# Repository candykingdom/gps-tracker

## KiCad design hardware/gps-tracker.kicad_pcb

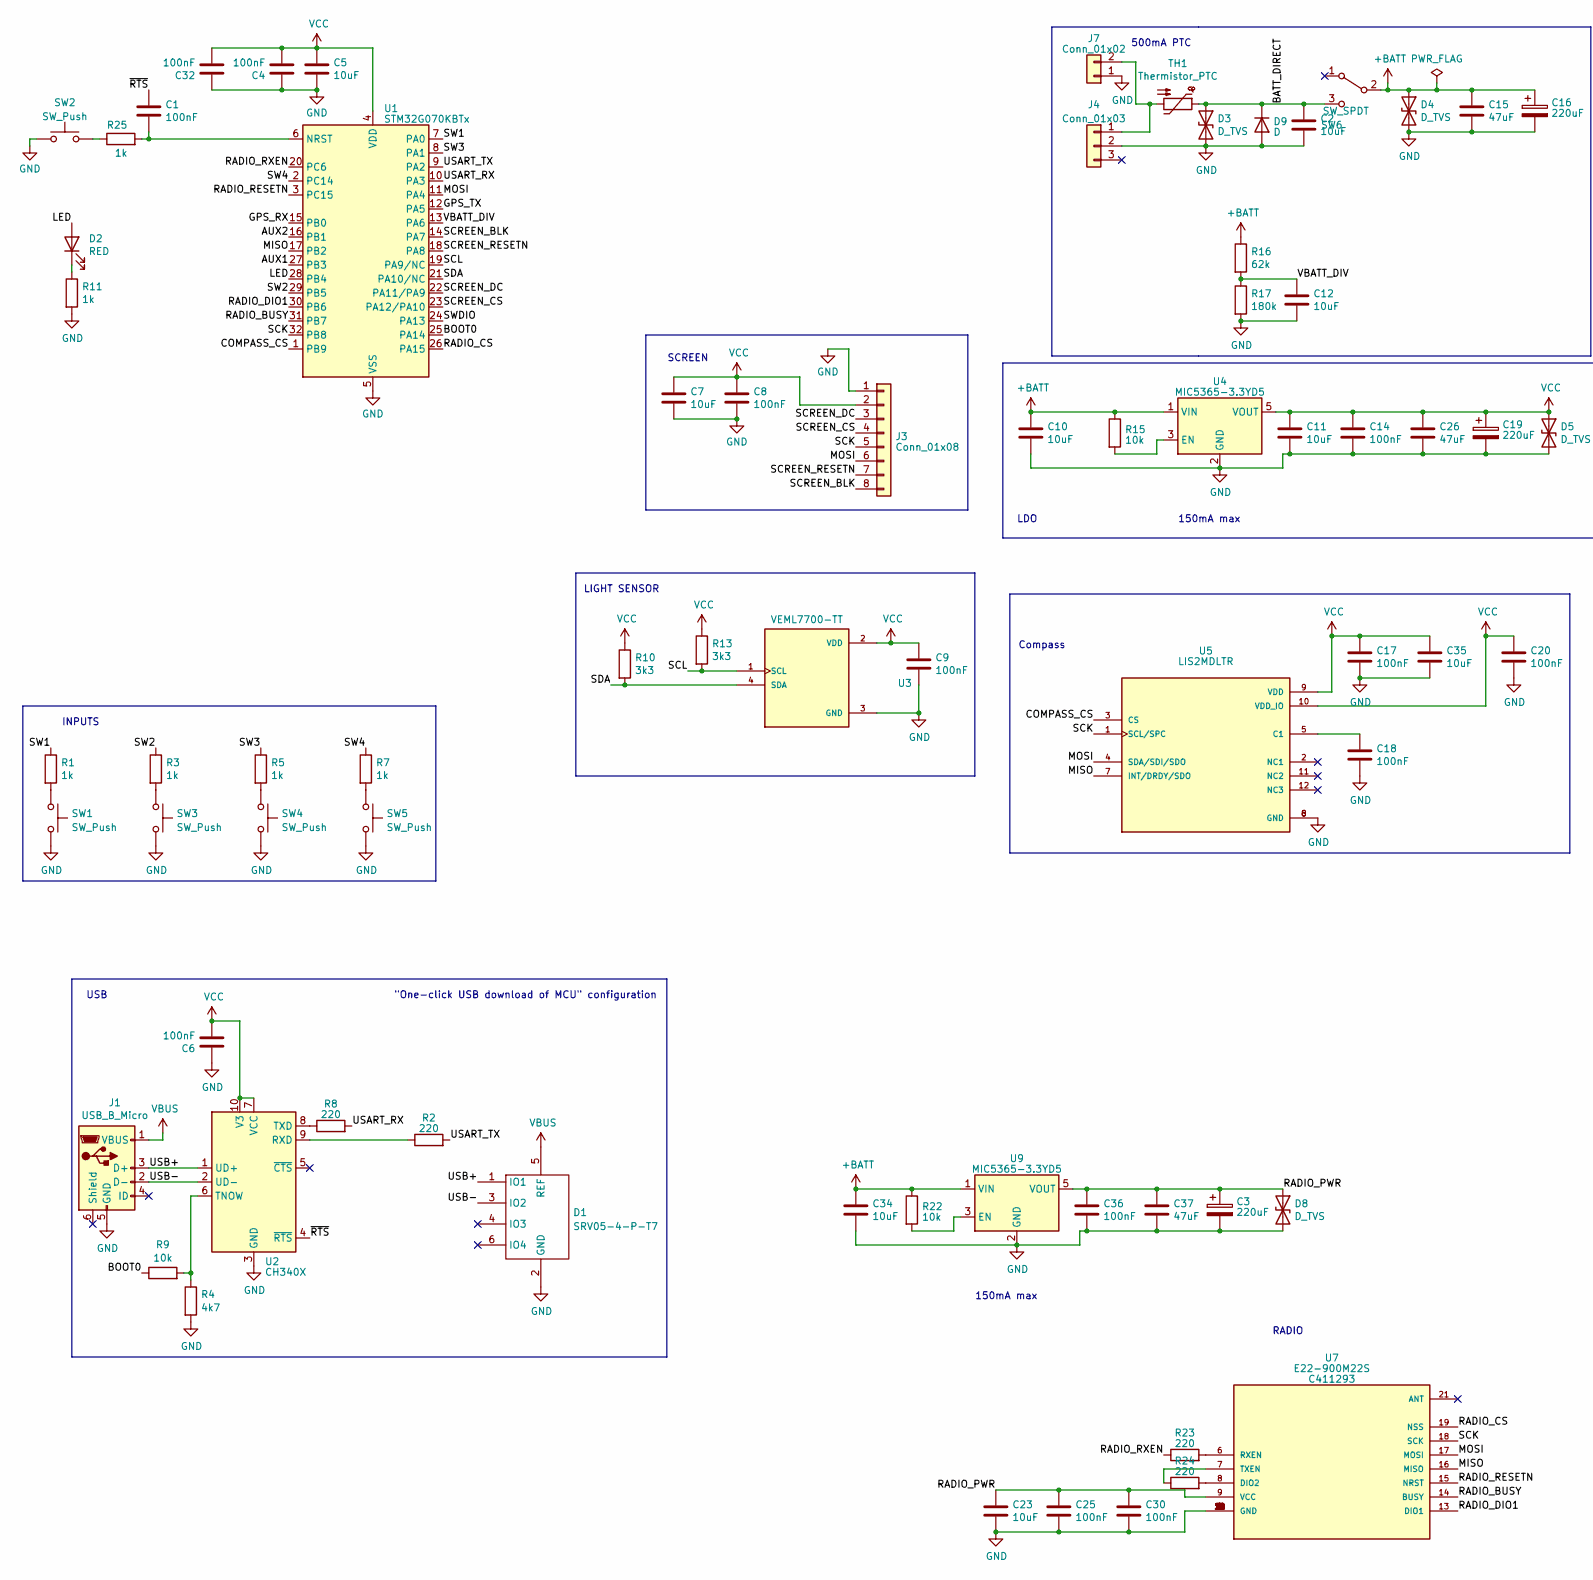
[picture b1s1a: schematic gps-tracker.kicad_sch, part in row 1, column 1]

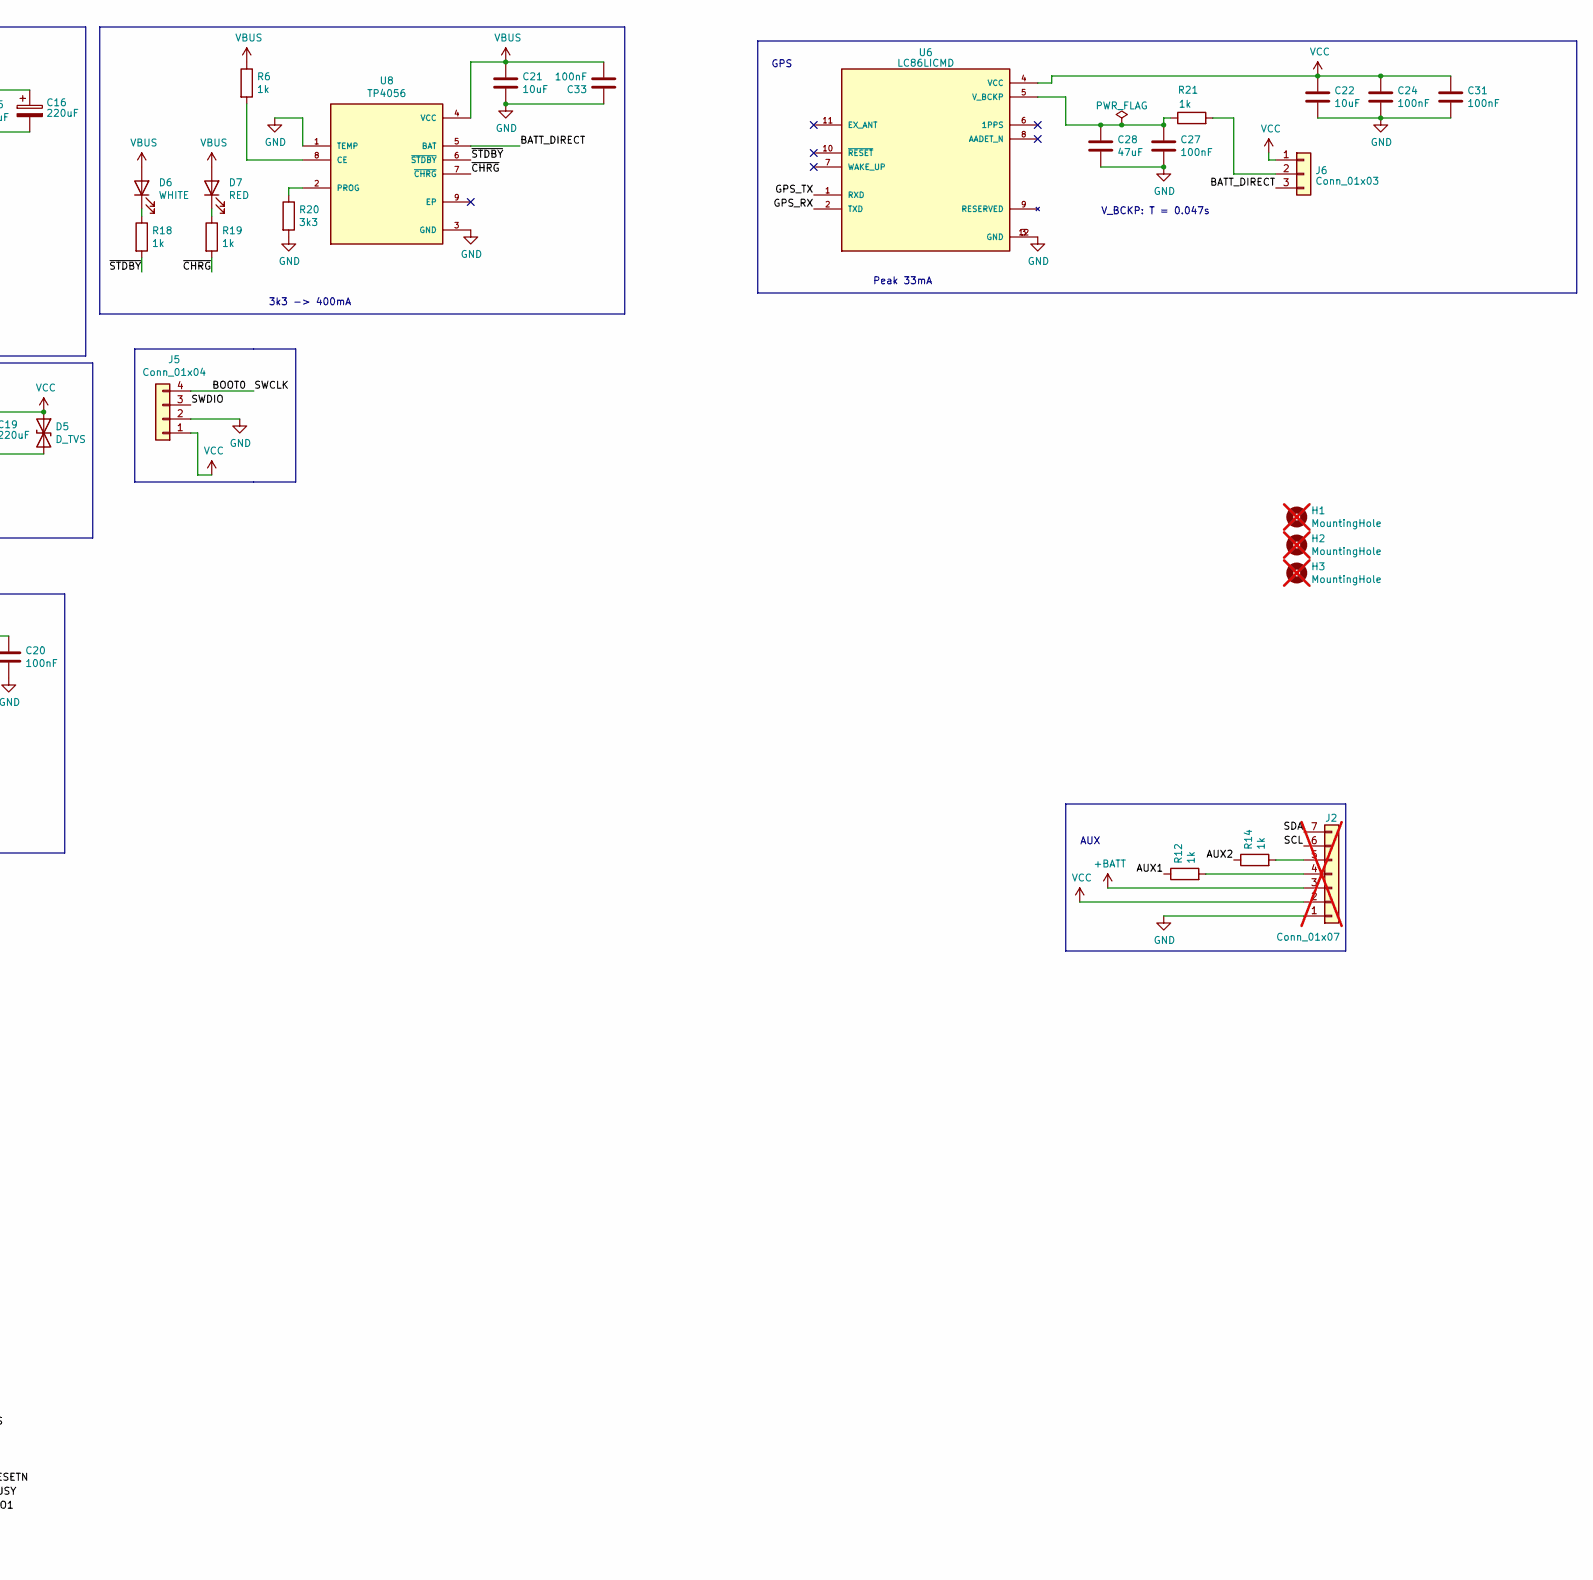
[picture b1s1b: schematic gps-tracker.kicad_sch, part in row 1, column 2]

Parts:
C1, C4, C6, C8, C9, C14, C17, C18, C20, C24, C25, C27, C30, C31, C32, C33, C36: 100nF; C_0402_1005Metric; LCSC C307331
C2, C5, C7, C10, C11, C12, C21, C22, C23, C34, C35: 10uF; C_0603_1608Metric; LCSC C96446
C3, C16, C19: 220uF; CP_Radial_D10.0mm_P5.00mm; MPN ER1E221MP51007RU
C15, C26, C28, C37: 47uF; C_1206_3216Metric; LCSC C96123
D1: SRV05-4-P-T7; SOT-23-6; LCSC C85364
D2, D7: RED; LED_0603_1608Metric; LCSC C2286
D3, D4, D5, D8: D_TVS; D_SOD-123F; LCSC C2990473
D6: WHITE; LED_0603_1608Metric; LCSC C2290
D9: D; D_SMA; LCSC C8678
H1, H2, H3: MountingHole; MountingHole_3.2mm_M3; not fitted
J1: USB_B_Micro; FRAMATOME_10118194-0001LF_fixed_bridges; LCSC C132563
J2: Conn_01x07; PinHeader_1x07_P2.54mm_Vertical; not fitted
J3: Conn_01x08; PinHeader_1x08_P2.54mm_Vertical
J4: Conn_01x03; MiniPV_78208-X03XXX_1x03_P2.54mm_Polarized_Horizontal
J5: Conn_01x04; PinHeader_1x04_P2.54mm_Vertical
J6: Conn_01x03; PinHeader_1x03_P2.54mm_Vertical
J7: Conn_01x02; JST_Micro_1x02_P1.25mm_Horizontal
R1, R3, R5, R6, R7, R11, R18, R19, R25: 1k; R_0402_1005Metric; LCSC C11702
R2, R8, R23, R24: 220; R_0402_1005Metric; LCSC C25091
R4: 4k7; R_0402_1005Metric; LCSC C25900
R9, R15, R22: 10k; R_0402_1005Metric; LCSC C25744
R10, R13, R20: 3k3; R_0603_1608Metric; LCSC C22978
R12, R14, R21: 1k; R_0603_1608Metric; LCSC C21190
R16: 62k; R_0603_1608Metric; LCSC C23221
R17: 180k; R_0603_1608Metric; LCSC C22827
SW1, SW2, SW3, SW4, SW5: SW_Push; SW_TACTILE_5.1MM_TS-1187A-C-D-B; LCSC C318884
SW6: SW_SPDT; SS-12D03-G5; LCSC C698226
TH1: Thermistor_PTC; Fuse_0805_2012Metric; LCSC C269104
U1: STM32G070KBTx; LQFP-32_7x7mm_P0.8mm; LCSC C529339
U2: CH340X; MSOP-10_3x3mm_P0.5mm; LCSC C3035748
U3: VEML7700-TT; VISHAY_VEML7700-TT; PARTREV 1.6
U4, U9: MIC5365-3.3YD5; SOT-23-5; MPN MIC5365-3.3YD5
U5: LIS2MDLTR; PQFN50P200X200X70-12N; PARTREV Rev 5; LCSC C919695
U6: LC86LICMD; MODULE_LC86LICMD; MPN LC86LICMD
U7: E22-900M22S; LCSC C411293
U8: TP4056; SOP-8_3.9x4.9mm_P1.27mm_Thermal; LCSC C382139

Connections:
+BATT: C10.2, C15.2, C16.1, C34.2, D4.1 (A1), J2.3, R15.1, R16.1, R22.1, SW6.2 (B), U4.1 (VIN), U9.1 (VIN)
/AUX1: R12.1, U1.27 (PB3)
/AUX2: R14.1, U1.16 (PB1)
/BATT_DIRECT: C2.2, D3.1 (A1), D9.1 (K), J6.3, SW6.3 (C), TH1.1, U8.5 (BAT)
/BOOT0: J5.4, R9.1, U1.25 (PA14)
/COMPASS_CS: U1.1 (PB9), U5.3 (CS)
/GPS_RX: U1.15 (PB0), U6.2 (TXD)
/GPS_TX: U1.12 (PA5), U6.1 (RXD)
/LED: D2.2 (A), U1.28 (PB4)
/MISO: U1.17 (PB2), U5.7 (INT/DRDY/SDO), U7.16 (MISO)
/MOSI: J3.6, U1.11 (PA4), U5.4 (SDA/SDI/SDO), U7.17 (MOSI)
/RADIO_BUSY: U1.31 (PB7), U7.14 (BUSY)
/RADIO_CS: U1.26 (PA15), U7.19 (NSS)
/RADIO_DIO1: U1.30 (PB6), U7.13 (DIO1)
/RADIO_PWR: C3.1, C23.2, C25.1, C30.1, C36.1, C37.2, D8.1 (A1), U7.9 (VCC), U9.5 (VOUT)
/RADIO_RESETN: U1.3 (PC15), U7.15 (NRST)
/RADIO_RXEN: R23.1, U1.20 (PC6)
/SCK: J3.5, U1.32 (PB8), U5.1 (SCL/SPC), U7.18 (SCK)
/SCL: J2.6, R13.2, U1.19 (PA9/NC), U3.1 (SCL)
/SCREEN_BLK: J3.8, U1.14 (PA7)
/SCREEN_CS: J3.4, U1.23 (PA12/PA10)
/SCREEN_DC: J3.3, U1.22 (PA11/PA9)
/SCREEN_RESETN: J3.7, U1.18 (PA8)
/SDA: J2.7, R10.2, U1.21 (PA10/NC), U3.4 (SDA)
/SW1: R1.1, U1.7 (PA0)
/SW2: R3.1, U1.29 (PB5)
/SW3: R5.1, U1.8 (PA1)
/SW4: R7.1, U1.2 (PC14)
/SWDIO: J5.3, U1.24 (PA13)
/USART_RX: R8.2, U1.10 (PA3)
/USART_TX: R2.2, U1.9 (PA2)
/USB+: D1.1 (IO1), J1.3 (D+), U2.1 (UD+)
/USB-: D1.3 (IO2), J1.2 (D-), U2.2 (UD-)
/VBATT_DIV: C12.2, R16.2, R17.1, U1.13 (PA6)
/~CHRG: R19.2, U8.7 (~CHRG)
/~RTS: C1.1, U2.4 (~RTS)
/~STDBY: R18.2, U8.6 (~STDBY)
GND: C2.1, C3.2, C4.1, C5.2, C6.1, C7.1, C8.2, C9.2, C10.1, C11.1, C12.1, C14.2, C15.1, C16.2, C17.2, C18.2, C19.2, C20.2, C21.1, C22.1, C23.1, C24.2, C25.2, C26.1, C27.2, C28.1, C30.2, C31.2, C32.1, C33.1, C34.1, C35.1, C36.2, C37.1, D1.2 (GND), D3.2 (A2), D4.2 (A2), D5.2 (A2), D8.2 (A2), D9.2 (A), J1.5 (GND), J2.1, J3.1, J4.2, J5.2, J7.1, R4.2, R11.2, R17.2, R20.2, SW1.2, SW2.1, SW3.2, SW4.2, SW5.2, U1.5 (VSS), U2.3 (GND), U3.3 (GND), U4.2 (GND), U5.6 (GND), U5.8 (GND), U6.3 (GND), U6.12 (GND), U7.1 (GND), U7.2 (GND), U7.3 (GND), U7.4 (GND), U7.5 (GND), U7.10 (GND), U7.11 (GND), U7.12 (GND), U7.20 (GND), U7.22 (GND), U8.1 (TEMP), U8.3 (GND), U9.2 (GND)
unnamed: D2.1 (K), R11.1
unnamed: D6.1 (K), R18.1
unnamed: D7.1 (K), R19.1
unnamed: J2.4, R12.2
unnamed: J2.5, R14.2
unnamed: J4.1, J7.2, TH1.2
unnamed: J6.2, R21.2
unnamed: R1.2, SW1.1
unnamed: R3.2, SW3.1
unnamed: R5.2, SW4.1
unnamed: R7.2, SW5.1
unnamed: R25.1, SW2.2
unnamed: C1.2, R25.2, U1.6 (NRST)
unnamed: R2.1, U2.9 (RXD)
unnamed: R4.1, R9.2, U2.6 (TNOW)
unnamed: R8.1, U2.8 (TXD)
unnamed: R15.2, U4.3 (EN)
unnamed: C18.1, U5.5 (C1)
unnamed: C27.1, C28.2, R21.1, U6.5 (V_BCKP)
unnamed: R24.2, U7.8 (DIO2)
unnamed: R23.2, U7.6 (RXEN)
unnamed: R24.1, U7.7 (TXEN)
unnamed: R6.2, U8.8 (CE)
unnamed: R20.1, U8.2 (PROG)
unnamed: R22.2, U9.3 (EN)
VBUS: C21.2, C33.2, D1.5 (REF), D6.2 (A), D7.2 (A), J1.1 (VBUS), R6.1, U8.4 (VCC)
VCC: C4.2, C5.1, C6.2, C7.2, C8.1, C9.1, C11.2, C14.1, C17.1, C19.1, C20.1, C22.2, C24.1, C26.2, C31.1, C32.2, C35.2, D5.1 (A1), J2.2, J3.2, J5.1, J6.1, R10.1, R13.1, U1.4 (VDD), U2.7 (VCC), U2.10 (V3), U3.2 (VDD), U4.5 (VOUT), U5.9 (VDD), U5.10 (VDD_IO), U6.4 (VCC)

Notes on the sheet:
Peak 33mA
RADIO
INPUTS
AUX
3k3 -> 400mA
USB
500mA PTC
LIGHT SENSOR
"One-click USB download of MCU" configuration
150mA max
GPS
Compass
V_BCKP: T = 0.047s
SCREEN
LDO

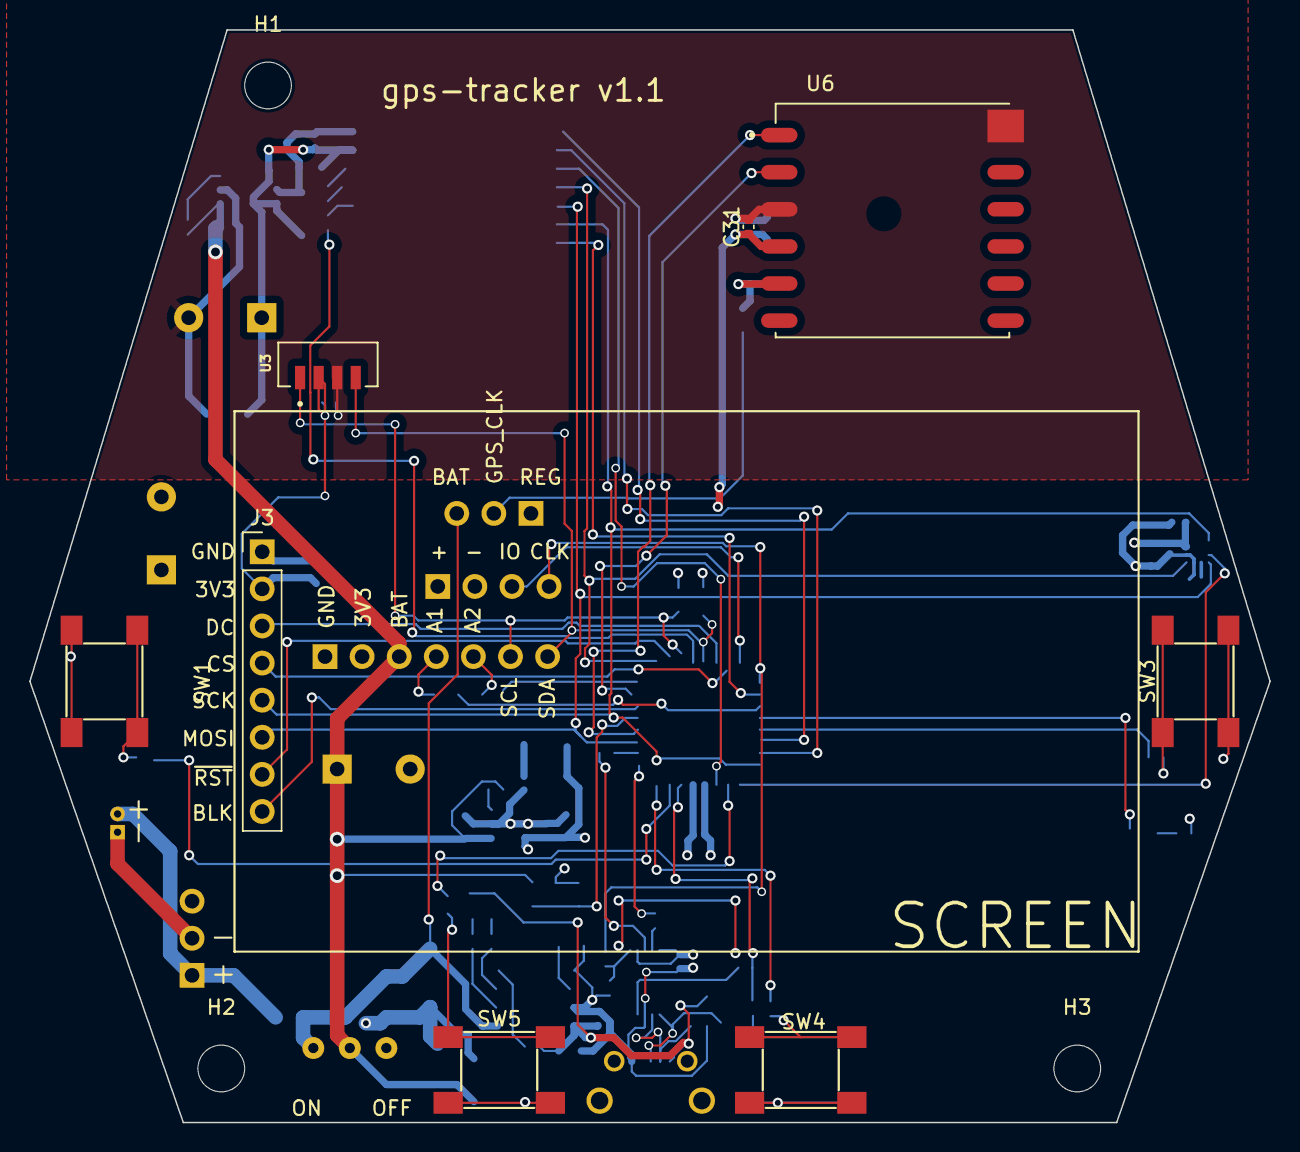
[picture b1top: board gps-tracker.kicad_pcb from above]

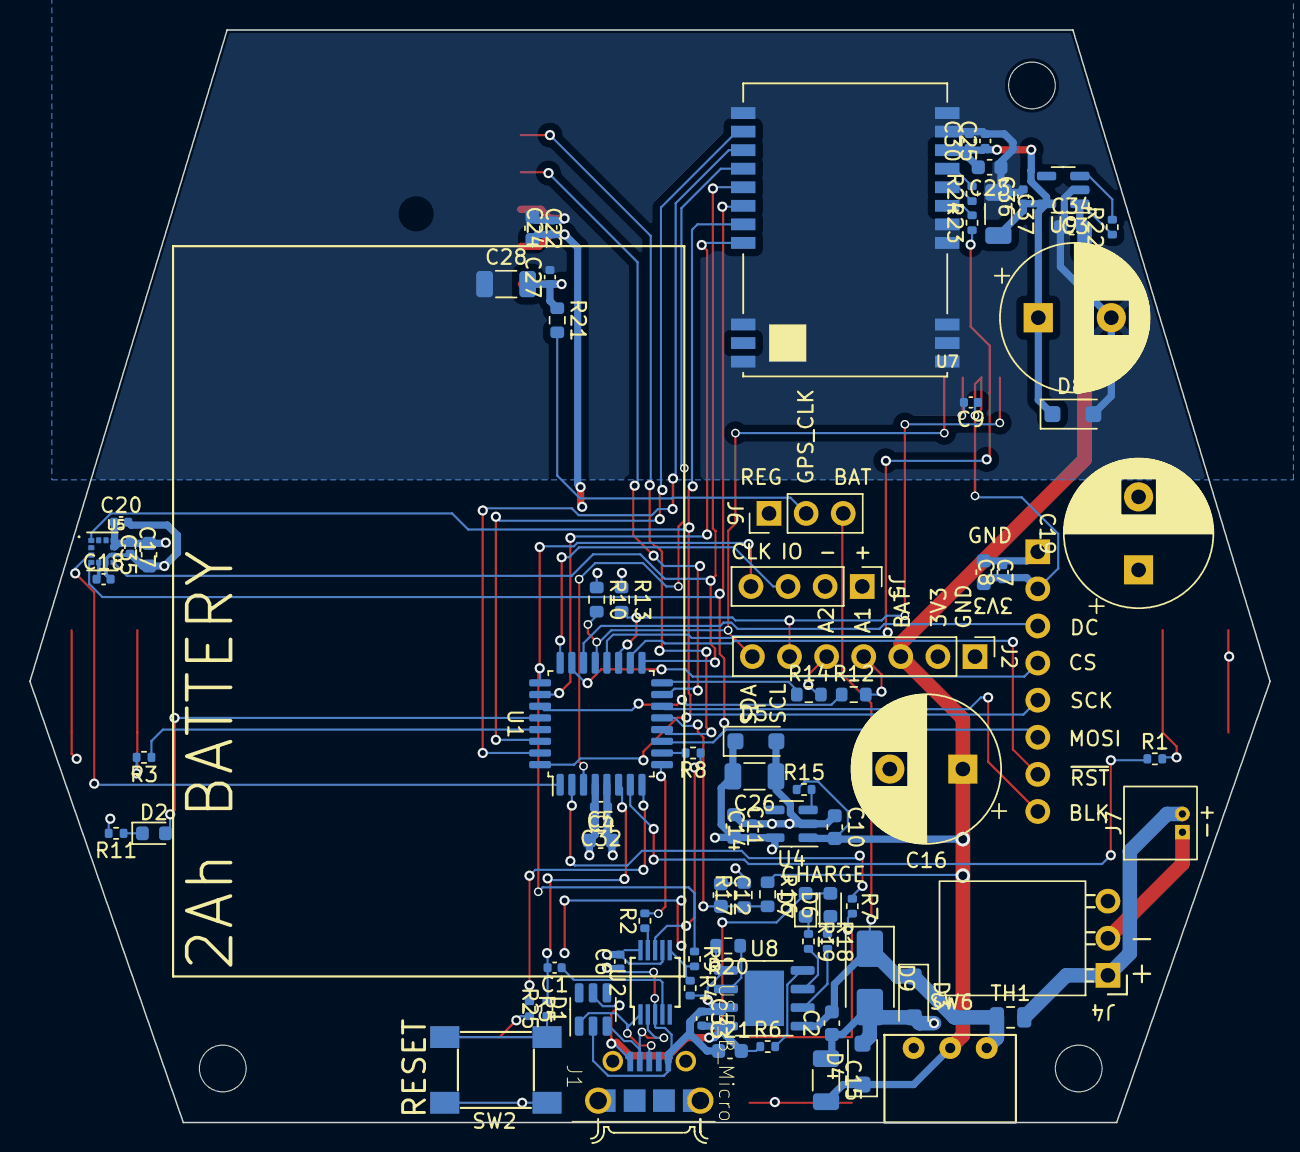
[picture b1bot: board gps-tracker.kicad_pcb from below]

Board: 4 copper layers, 84.9 x 74.8 mm, 95 parts (84 on the bottom side), 65 nets.

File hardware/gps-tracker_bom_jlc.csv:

"Comment","Designator","Footprint","LCSC Part #"
"100nF","C1,C4,C6,C8,C9,C14,C17,C18,C20,C24,C25,C27,C30,C31,C32,C33,C36","C_0402_1005Metric","C307331"
"10uF","C2,C5,C7,C10,C11,C12,C21,C22,C23,C34,C35","C_0603_1608Metric","C96446"
"47uF","C15,C26,C28,C37","C_1206_3216Metric","C96123"
"SRV05-4-P-T7","D1","SOT-23-6","C85364"
"RED","D2,D7","LED_0603_1608Metric","C2286"
"D_TVS","D3,D4,D5,D8","D_SOD-123F","C2990473"
"WHITE","D6","LED_0603_1608Metric","C2290"
"D","D9","D_SMA","C8678"
"USB_B_Micro","J1","FRAMATOME_10118194-0001LF_fixed_bridges","C132563"
"1k","R1,R3,R5,R6,R7,R11,R18,R19,R25","R_0402_1005Metric","C11702"
"220","R2,R8,R23,R24","R_0402_1005Metric","C25091"
"4k7","R4","R_0402_1005Metric","C25900"
"10k","R9,R15,R22","R_0402_1005Metric","C25744"
"3k3","R10,R13,R20","R_0603_1608Metric","C22978"
"1k","R12,R14,R21","R_0603_1608Metric","C21190"
"62k","R16","R_0603_1608Metric","C23221"
"180k","R17","R_0603_1608Metric","C22827"
"SW_Push","SW1,SW2,SW3,SW4,SW5","SW_TACTILE_5.1MM_TS-1187A-C-D-B","C318884"
"SW_SPDT","SW6","SS-12D03-G5","C698226"
"Thermistor_PTC","TH1","Fuse_0805_2012Metric","C269104"
"STM32G070KBTx","U1","LQFP-32_7x7mm_P0.8mm","C529339"
"CH340X","U2","MSOP-10_3x3mm_P0.5mm","C3035748"
"LIS2MDLTR","U5","PQFN50P200X200X70-12N","C919695"
"E22-900M22S","U7","E22-900M22S","C411293"
"TP4056","U8","SOP-8_3.9x4.9mm_P1.27mm_Thermal","C382139"

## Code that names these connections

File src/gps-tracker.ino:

#include <Adafruit_GFX.h>  // Core graphics library
#include <Adafruit_LTR329_LTR303.h>
#include <Adafruit_ST7789.h>  // Hardware-specific library for ST7789
#include <Arduino.h>
#include <RadioLib.h>
#include <TinyGPSPlus.h>

#include <algorithm>

#include "arduino-compass.h"
#include "arduino-gps.h"
#include "radio.h"

constexpr bool kUseScreen = false;

constexpr int kLed = PB4;

// SPI
constexpr int kMiso = PB2;
constexpr int kMosi = PA4;
constexpr int kSck = PB8;

// Radio
constexpr int kRadioCs = PA15;
constexpr int kRadioDio1 = PB6;
constexpr int kRadioBusy = PB7;
constexpr int kRadioRxen = PC6;

// Screen
constexpr int kScreenDc = PA11;
constexpr int kScreenCs = PA12;
constexpr int kScreenBlk = PA7;
constexpr int kScreenReset = PA8;
Adafruit_ST7789 screen = Adafruit_ST7789(kScreenCs, kScreenDc, kScreenReset);

// I2C
constexpr int kScl = PA9;
constexpr int kSda = PA10;

Adafruit_LTR303 light_sensor;
ArduinoCompass compass;
ArduinoGps gps;

SPISettings radio_spi_settings(10 * 1000 * 1000, MSBFIRST, SPI_MODE0);
SX1262 radio = new Module(kRadioCs, kRadioDio1, /*rst=*/RADIOLIB_NC,
                          /*gpio=*/kRadioBusy, SPI, radio_spi_settings);
volatile bool radio_idle = true;

void SetRadioIdle(void) {
  radio_idle = true;
  // digitalWrite(kLed, LOW);
}

void FatalError() {
  bool on = false;
  while (true) {
    digitalWrite(kLed, on);
    delay(100);
    on = !on;
  }
}

// http://www.hhhh.org/wiml/proj/nmeaxor.html
String withChecksum(String sentence) {
  bool started = false;
  char checksum = 0;
  for (uint32_t index = 0; index < sentence.length(); index++) {
    if (index > 0 && sentence[index - 1] == '$') {
      checksum = sentence[index];
      started = true;
      continue;  // Skip the rest of this loop iteration.
    }

    if (sentence[index] == '*') {
      break;  // Exit the loop.
    }

    // Ignore everything preceeding '$'.
    if (!started) {
      continue;  // Skip the rest of this loop iteration.
    }

    checksum = checksum xor sentence[index];
  }

  String sentenceWithChecksum =
      sentence + (checksum < 10 ? "0" : "") + String(checksum, HEX);
  return sentenceWithChecksum;
}

void ConfigureScreen() {
  screen.init(/*width=*/240, /*height=*/320);
  screen.setSPISpeed(20 * 1000 * 1000);
  screen.fillScreen(ST77XX_BLACK);
  screen.setTextSize(2);
  screen.setTextWrap(false);
}

void setup() {
  // check if nBOOT_SEL bit is set
  if (FLASH->OPTR & FLASH_OPTR_nBOOT_SEL) {
    // unlock flash/option
    FLASH->KEYR = 0x45670123;
    FLASH->KEYR = 0xCDEF89AB;
    FLASH->OPTKEYR = 0x08192A3B;
    FLASH->OPTKEYR = 0x4C5D6E7F;

    while (FLASH->SR & FLASH_SR_BSY1)
      ;

    // clear nBOOT_SEL bit
    FLASH->OPTR &= ~FLASH_OPTR_nBOOT_SEL;

    // write
    FLASH->CR |= FLASH_CR_OPTSTRT;
    while (FLASH->SR & FLASH_SR_BSY1)
      ;
  }

  pinMode(kLed, OUTPUT);
  // digitalWrite(kLed, HIGH);
  pinMode(kScreenBlk, OUTPUT);
  digitalWrite(kScreenBlk, HIGH);

  pinMode(kRadioRxen, OUTPUT);
  digitalWrite(kRadioRxen, HIGH);

  Serial2.begin(115200);
  Serial2.printf("Booting...\n");

  SPI.setMISO(kMiso);
  SPI.setMOSI(kMosi);
  SPI.setSCLK(kSck);

  delay(100);
  // TODO: re-enable when light sensor can be soldered reliably
  // Wire.setSCL(kScl);
  // Wire.setSDA(kSda);
  // Wire.begin();
  // Wire.setClock(100000);
  // if (!light_sensor.begin()) {
  //   Serial2.println("Light sensor init failed");
  //   FatalError();
  // }
  // light_sensor.setGain(LTR3XX_GAIN_1);
  // light_sensor.setIntegrationTime(LTR3XX_INTEGTIME_400);
  // light_sensor.setMeasurementRate(LTR3XX_MEASRATE_500);

  if (!compass.Begin()) {
    Serial2.println("Failed to initialize compass");
    FatalError();
  }

  if (!gps.Begin()) {
    Serial2.println("Failed to initialize GPS");
    FatalError();
  }

  // Configure radio
  Serial2.print("Initializing radio... ");
  int state = radio.begin(/*freq=*/915.0, /*bw*/ 125, /*sf=*/9, /*cr=*/7,
                          /*syncWord=*/18, /*power=*/22, /*preambleLength=*/8,
                          /*txcoVoltage=*/1.8, /*useRegulatorLdo=*/false);
  if (state == RADIOLIB_ERR_NONE) {
    Serial2.println("success.");
  } else {
    Serial2.print("failed, code ");
    Serial2.println(state);
    FatalError();
  }
  radio.setDio1Action(SetRadioIdle);
  radio.setRfSwitchPins(kRadioRxen, RADIOLIB_NC);
  state = radio.setDio2AsRfSwitch(true);
  if (state != RADIOLIB_ERR_NONE) {
    Serial2.printf("`radio.setDio2AsRfSwitch` failed: %d\n");
  }
  radio.startReceive();

  // digitalWrite(kLed, LOW);

  if (kUseScreen) {
    ConfigureScreen();
  }
}

void DisplayCompass() {
  static constexpr float kCircleRadius = 100;
  static constexpr int16_t kCompassCenterX = 120;
  static constexpr int16_t kCompassCenterY = 160;
  static int16_t compass_x = 0;
  static int16_t compass_y = 0;
  static float heading = 0;

  screen.drawLine(kCompassCenterX, kCompassCenterY, compass_x, compass_y,
                  ST77XX_BLACK);

  heading = compass.GetHeadingRadians();
  compass_x = kCompassCenterX + kCircleRadius * cos(2 * 3.141593 - heading);
  compass_y = kCompassCenterY + kCircleRadius * sin(2 * 3.141593 - heading);
  screen.drawLine(kCompassCenterX, kCompassCenterY, compass_x, compass_y,
                  ST77XX_WHITE);

  screen.fillRect(/*x=*/0, /*y=*/0, /*w=*/50, /*h=*/15, ST77XX_BLACK);
  screen.setCursor(0, 0);
  screen.setTextColor(ST77XX_WHITE);
  screen.printf("%3d", (int16_t)Compass::RadiansToDegrees(heading));
}

void DumpLightSensor() {
  bool valid;
  uint16_t visible_plus_ir, infrared;

  if (light_sensor.newDataAvailable()) {
    valid = light_sensor.readBothChannels(visible_plus_ir, infrared);
    if (valid) {
      Serial2.print("CH0 Visible + IR: ");
      Serial2.print(visible_plus_ir);
      Serial2.print("\t\tCH1 Infrared: ");
      Serial2.println(infrared);
    } else {
      Serial2.println("Light sensor data invalid");
    }
  }
}

uint32_t print_at = 0;
constexpr uint32_t kPrintEvery = 1000;

uint32_t screen_update_at = 0;
constexpr uint32_t kScreenUpdateEvery = 500;

uint32_t received_packet_at = 0;
uint32_t force_send_packet_at = 4000;
int16_t last_rssi = 0;
int16_t last_snr = 0;

void Transmit() {
  Serial2.printf("Transmitting... (%d)\n", radio_idle);
  // digitalWrite(kRadioRxen, LOW);
  // delay(1);
  int state = radio.startTransmit("test message");
  if (state == RADIOLIB_ERR_NONE) {
    Serial2.println("Radio start transmit success!");
  } else {
    Serial2.printf("Radio transmit failed, code: %d\n", state);
  }
  // digitalWrite(kRadioRxen, HIGH);
  // delay(1);
}

constexpr float kLatitude = 0;
constexpr float kLongitude = 0;

void loop() {
  static bool last_op_transmit = false;

  // int state = radio.startReceive();
  // if (state == RADIOLIB_ERR_NONE) {
  //   Serial2.println("Radio receive success!");
  // } else {
  //   Serial2.print("Radio receive failed, code ");
  //   Serial2.println(state);
  //   delay(500);
  // }

  gps.Step();

  if (millis() > 3000 && radio_idle) {
    radio_idle = false;
    if (last_op_transmit) {
      Serial2.println("Starting receive");
      last_op_transmit = false;
      radio.startReceive();
    } else {
      // We received a packet
      received_packet_at = millis();
      String received;
      int state = radio.readData(received);
      if (state == RADIOLIB_ERR_NONE) {
        Serial2.print("*** Received: ");
        Serial2.println(received);
        digitalWrite(kLed, HIGH);
        delay(10);
        digitalWrite(kLed, LOW);
        delay(10);
      }
      last_rssi = radio.getRSSI();
      last_snr = radio.getSNR();
      radio.standby();
      last_op_transmit = true;
      Transmit();
    }
  }

  if (!last_op_transmit && millis() > force_send_packet_at) {
    force_send_packet_at = millis() + 500 + random(100);
    radio.standby();
    last_op_transmit = true;
    Transmit();
  }

  if (millis() > print_at) {
    Serial2.println(millis());
    print_at = millis() + kPrintEvery;
  }

  digitalWrite(kLed, (millis() / 100) % 25 == 0);

  if (kUseScreen && millis() > screen_update_at) {
    // DisplayCompass();

    screen.fillRect(/*x=*/0, /*y=*/0, /*w=*/120, /*h=*/64, ST77XX_BLACK);
    screen.setCursor(0, 0);
    screen.setTextColor(ST77XX_WHITE);
    screen.printf("Up: %6u\n", millis() - received_packet_at);
    screen.printf("RSSI: %4d\n", last_rssi);
    screen.printf("SNR:  %4d\n", last_snr);
    Coordinates coordinates = gps.GetCoordinates();
    if (coordinates.valid) {
      screen.printf("Dis: %5d", (int32_t)TinyGPSPlus::distanceBetween(
                                    coordinates.latitude, coordinates.longitude,
                                    kLatitude, kLongitude));
    }

    screen_update_at = millis() + kScreenUpdateEvery;
  }
}

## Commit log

2023-02-16 Start defining schematic - add processor
2023-02-19 First pass at schematic
2023-02-19 Update part numbers and footprints
2023-02-19 Add gitignore for software
2023-02-20 Update to lower-power SPI radio module
2023-02-25 First pass at PCB positions
2023-04-07 Hardware v1.0
2023-04-07 Some fixes for hardware v1.0
2023-04-07 Include CSV files
2023-04-07 Fix compass rotation in cpl
2023-04-19 Add 3d model for pcb
2023-04-21 Add software; read from compass
2023-07-13 Add test code for light sensor
2023-07-13 Add a function for hard-iron calibrating the compass
2023-07-14 Add basic GPS functionality
2023-07-14 Update GPS dump to include comms info
2023-07-14 Add more GPS debugging
2023-07-14 Fix GPS location dump to not sleep
2023-07-14 Configure the GPS
2023-07-15 Pin the TinyGPS++ library version
2023-07-15 Ignore more KiCAD temp files
2023-07-15 Initialize radio
2023-07-15 Remove GPS config debug code
2023-07-15 Debug radio transmit
2023-07-15 Add support for screen
2023-07-15 Add compass display on screen
2023-07-15 Fix compass display
2023-07-15 Move compass display to a function
2023-07-20 Add LoRa distance tester
2023-07-22 Hardware revision v1.1:
    - Switch to (hopefully) easier-to-solder light sensor
    - Fix bootloader situation: use "One-click USB download of MCU" configuration from CH340 datasheet
    - Connect radio reset line to MCU
    - (Slightly) increase clearance for hand-soldering voltage regulators
2023-07-30 Update radio range test
2023-07-30 Move compass into a library
2023-07-30 Add test coverage for Compass::RadiansToDegrees
2023-07-30 Add a CI config
2023-07-30 Extract gps into a library
2023-08-02 Add library and basic hal for radio
2023-08-04 Add test for radio initialization
2023-08-04 Add transmit to radio, with test coverage
2023-08-04 Add receive to radio, with test coverage
2023-08-04 Add radio standby
2023-08-04 Add documentation for radio power consumption
